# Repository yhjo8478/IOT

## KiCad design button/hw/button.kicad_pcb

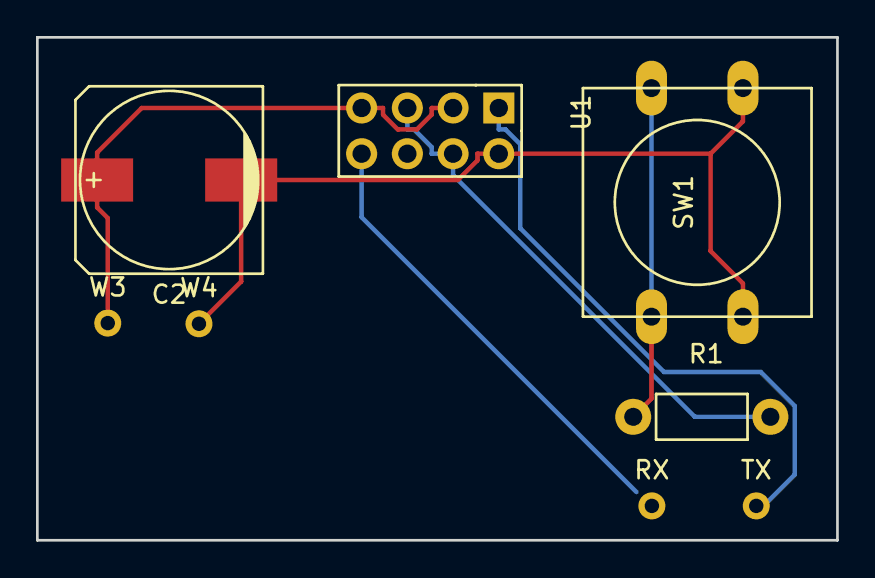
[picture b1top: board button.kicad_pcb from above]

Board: 2 copper layers, 44.5 x 27.9 mm, 8 parts (0 on the bottom side), 6 nets.

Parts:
C2: 1000uF; c_elec_10x10
R1: 10; Resistor_Horizontal_RM7mm
RX: RX; Measurement_Point_Round-TH_Small
SW1: SW_PUSH; SW_PUSH-12mm
TX: TX; Measurement_Point_Round-TH_Small
U1: ESP-01v090; ESP-01
W3: VBAT; Measurement_Point_Round-TH_Small
W4: GBAT; Measurement_Point_Round-TH_Small

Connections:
/SWT_IN: R1.2, U1.4, U1.5
GND: C2.2, SW1.2, U1.2, W4.1
unnamed: R1.1, SW1.1
unnamed: TX.1, U1.1
unnamed: RX.1, U1.8
VCC: C2.1, U1.3, U1.7, W3.1

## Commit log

2016-07-24 esp8266 wifi button added
2016-07-26 [button][sw] Give delay btw toggle button. If can nott connect wifi, goto deep sleep
